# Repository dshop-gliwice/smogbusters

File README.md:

# smogbusters
Air monitoring project

Links:
 - particulate matter (PM) map: http://smogbusters.org/
 - charts: http://grafana.smogbusters.org/dashboard/db/measurements?refresh=10s&orgId=1
 - list of components: [bom.md](./docs/bom.md)

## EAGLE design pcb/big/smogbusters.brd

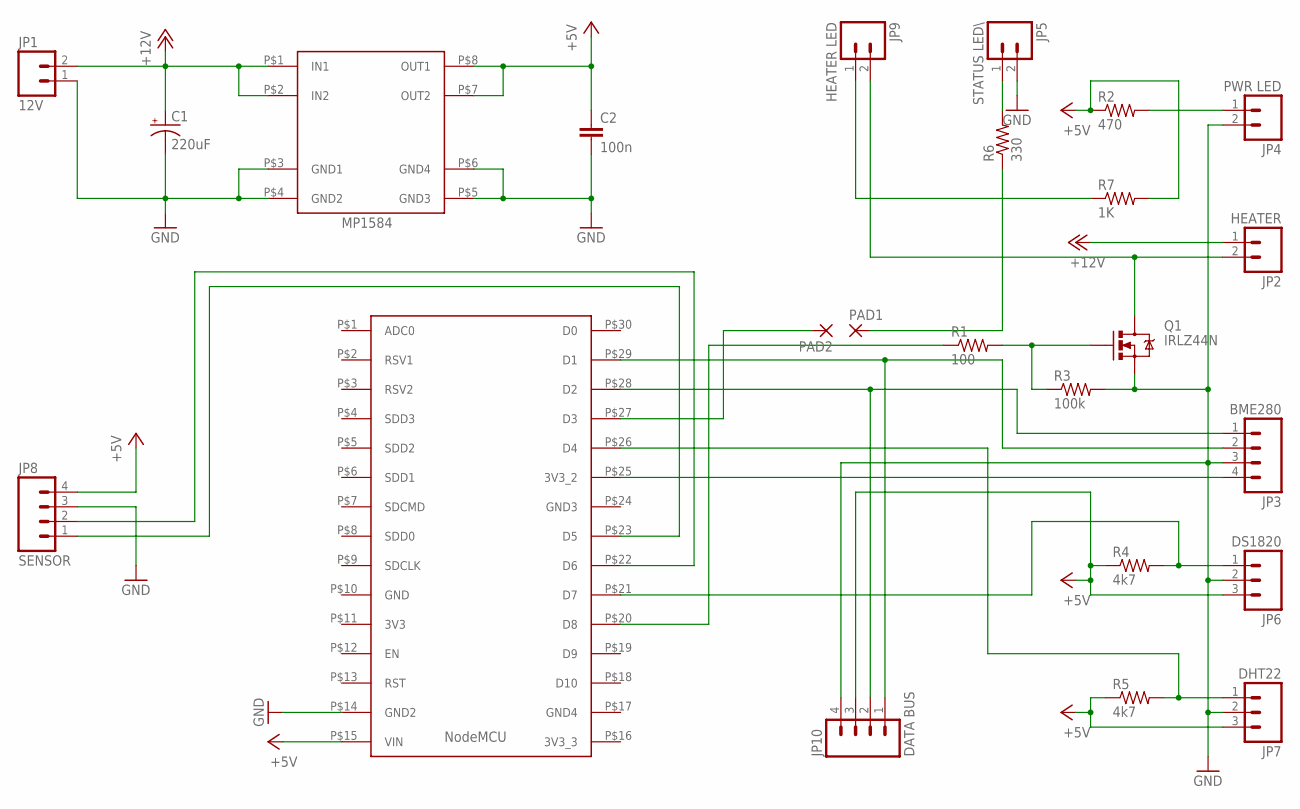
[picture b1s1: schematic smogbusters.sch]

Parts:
C1: 220uF; CPOL-RADIAL-100UF-25V
C2: 100n; C5B2.5
JP1: 12V; SCREWTERMINAL-5MM-2
JP2: HEATER; SCREWTERMINAL-5MM-2
JP3: BME280; 1X04
JP4: PWR LED; 1X02
JP5: STATUS LED\; 1X02
JP6: DS1820; 1X03
JP7: DHT22; 1X03
JP8: SENSOR; MOLEX-1X4
JP9: HEATER LED; 1X02
JP10: DATA BUS; 1X04
PAD1, PAD2: 1,6/0,8
Q1: IRLZ44N; TO220V
R1: 100; AXIAL-0.3
R2: 470; AXIAL-0.3
R3: 100k; AXIAL-0.3
R4, R5: 4k7; AXIAL-0.3
R6: 330; AXIAL-0.3
R7: 1K; AXIAL-0.3
U$1: NODEMCU
U$2: MP1584

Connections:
+5V: C2.1, JP6.3, JP7.3, JP8.4, JP10.3, R2.P$1 (1), R4.P$1 (1), R5.P$1 (1), R7.P$2 (2), U$1.P$15 (VIN), U$2.P$7 (OUT2), U$2.P$8 (OUT1)
+12V: C1.1 (+), JP1.2, JP2.1, U$2.P$1 (IN1), U$2.P$2 (IN2)
GND: C1.2 (-), C2.2, JP1.1, JP3.3, JP4.2, JP5.2, JP6.2, JP7.2, JP8.3, JP10.4, Q1.3 (S), R3.P$2 (2), U$1.P$14 (GND2), U$2.P$3 (GND1), U$2.P$4 (GND2), U$2.P$5 (GND3), U$2.P$6 (GND4)
unnamed: JP2.2, JP9.2, Q1.2 (D)
unnamed: JP6.1, R4.P$2 (2), U$1.P$21 (D7)
unnamed: Q1.1 (G), R1.P$2 (2), R3.P$1 (1)
unnamed: JP5.1, R6.P$2 (2)
unnamed: JP3.4, U$1.P$25 (3V3_2)
unnamed: JP8.1, U$1.P$23 (D5)
unnamed: JP8.2, U$1.P$22 (D6)
unnamed: R1.P$1 (1), U$1.P$20 (D8)
unnamed: JP7.1, R5.P$2 (2), U$1.P$26 (D4)
unnamed: PAD1.1, R6.P$1 (1)
unnamed: JP9.1, R7.P$1 (1)
unnamed: PAD2.1, U$1.P$27 (D3)
unnamed: JP4.1, R2.P$2 (2)
unnamed: JP3.1, JP10.2, U$1.P$28 (D2)
unnamed: JP3.2, JP10.1, U$1.P$29 (D1)

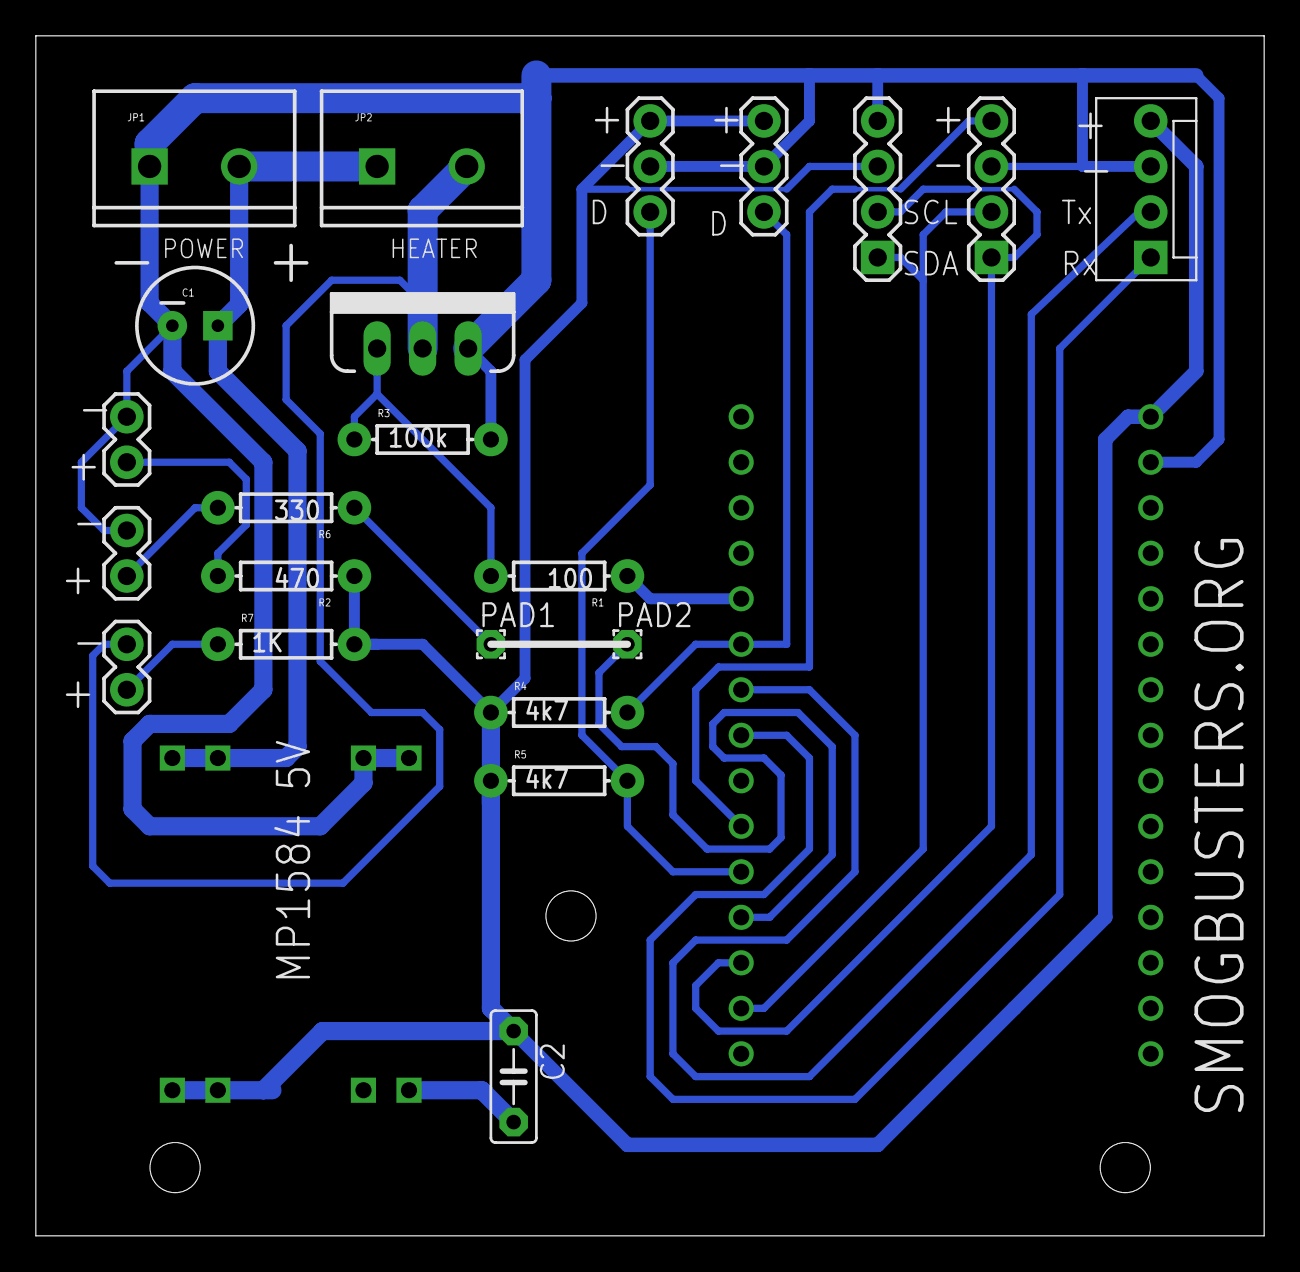
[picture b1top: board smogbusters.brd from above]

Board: 1 copper layer, 68.6 x 67.0 mm, 24 parts (1 on the bottom side), 18 nets.

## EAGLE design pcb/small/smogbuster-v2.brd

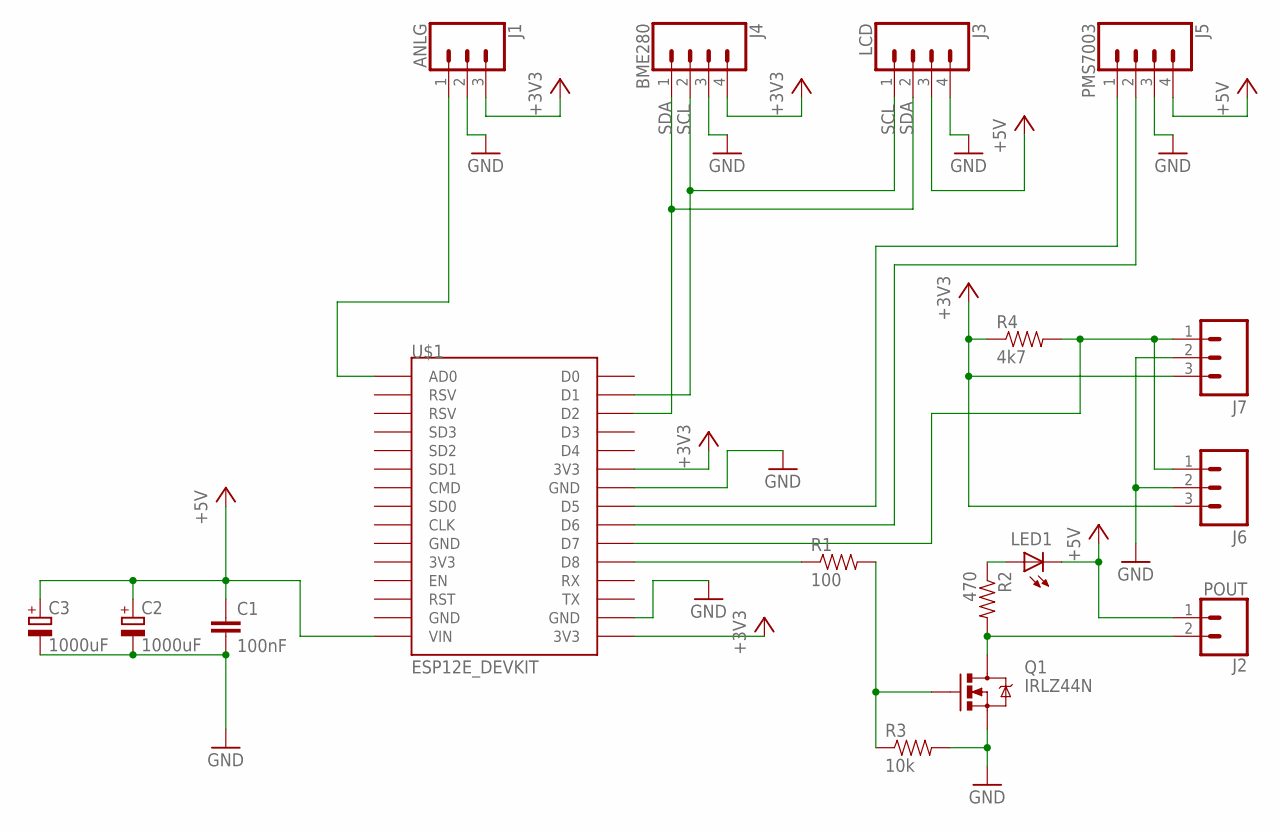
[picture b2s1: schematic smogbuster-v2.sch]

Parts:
C1: 100nF; CAP-PTH-5MM
C2, C3: 1000uF; E2,5-7
J1: ANLG; 1X03
J2: POUT; 1X02
J3: LCD; 1X04
J4: BME280; 1X04
J5: PMS7003; 1X04
J6, J7: M03PTH; 1X03
LED1: LED3MM
Q1: IRLZ44N; TO220V
R1: 100; AXIAL-0.3
R2: 470; AXIAL-0.3
R3: 10k; AXIAL-0.3
R4: 4k7; AXIAL-0.3
U$1: ESP12E_DEVKIT

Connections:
+3V3: J1.3, J4.4, J6.3, J7.3, R4.P$1 (1), U$1.3V3@1 (3V3), U$1.3V3@2 (3V3)
+5V: C1.1, C2.+, C3.+, J2.1, J3.3, J5.4, LED1.K (C), U$1.VIN
DQ: J6.1, J7.1, R4.P$2 (2), U$1.D7
GND: C1.2, C2.-, C3.-, J1.2, J3.4, J4.3, J5.3, J6.2, J7.2, Q1.3 (S), R3.P$2 (2), U$1.GND@2 (GND), U$1.GND@3 (GND)
unnamed: J2.2, Q1.2 (D), R2.P$2 (2)
unnamed: Q1.1 (G), R1.P$2 (2), R3.P$1 (1)
unnamed: J1.1, U$1.AD0
unnamed: R1.P$1 (1), U$1.D8
unnamed: LED1.A, R2.P$1 (1)
RX: J5.1, U$1.D5
SCL: J3.1, J4.2, U$1.D1
SDA: J3.2, J4.1, U$1.D2
TX: J5.2, U$1.D6

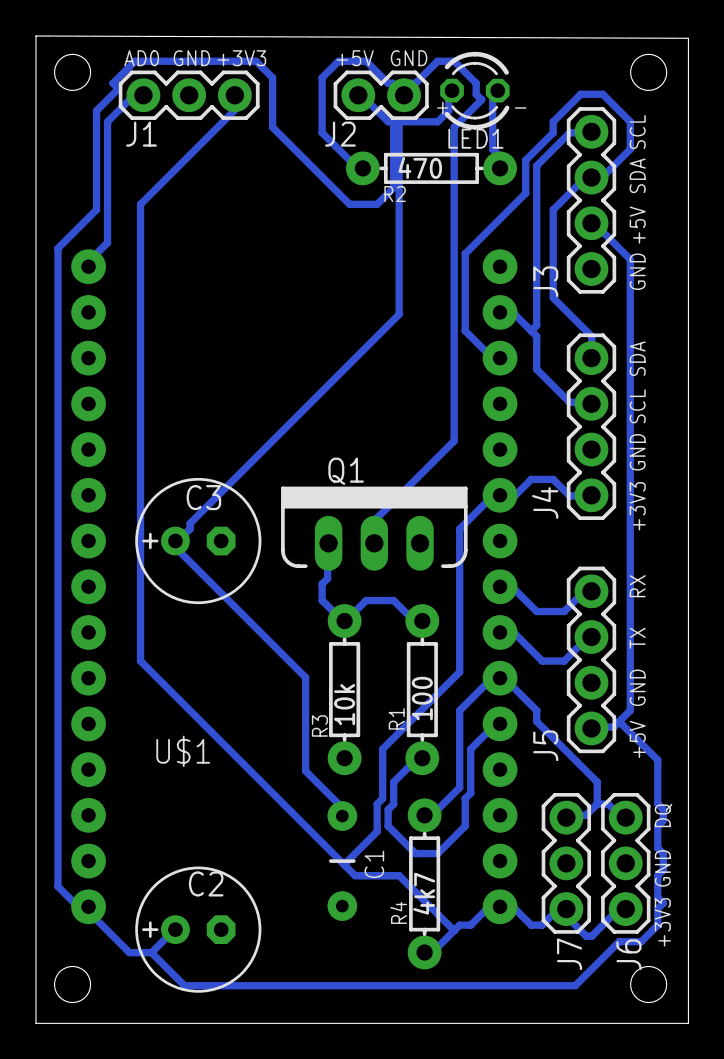
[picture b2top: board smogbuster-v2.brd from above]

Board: 1 copper layer, 36.2 x 54.9 mm, 17 parts (0 on the bottom side), 13 nets.

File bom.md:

# smogbusters
Air monitoring project

* NodeMCU
  * https://www.aliexpress.com/item/1PCS-New-Wireless-Module-Nod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
  * https://botland.com.pl/moduly-wifi/4450-modul-wifi-esp8266-n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


* Mosfet IRLZ44N
  * https://www.aliexpress.com/item/10PCS-IRLZ44N-IRLZ44-TO-220-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
  * https://botland.com.pl/n-mosfet/1950-n-mosfet-irlz44n-tht.ht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


* DC Power Supply Socket Female - 5.5 x 2.1mm
  * https://www.aliexpress.com/item/10Pcs-5-5-x-2-1mm-DC-Power-S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
  * https://botland.com.pl/przewody-i-zlacza-zasilajace/9352-gni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


* 15 Pin Female Single Row Straight Header Strip 2.54mm Pitch  
  * https://www.aliexpress.com/snapshot/0.html?spm=a2g0s.9042311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


* ARK connector
  * https://www.aliexpress.com/item/20pcs-KF301-2-Pin-Screw-Term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
  * https://botland.com.pl/zlacza-ark/810-zlacze-kf301-raster-5-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


* Wires
  * https://botland.com.pl/przewody-polaczeniowe/2713-przewod-ze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


* Power supply
  * https://www.aliexpress.com/item/S103-1pc-New-AC-100-240V-to-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


* BME280
  * https://www.aliexpress.com/item/BME280-Digital-Sensor-Temper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
  * https://botland.com.pl/czujniki-temperatury/165-czujnik-temp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


* DS18B20
  * https://www.aliexpress.com/item/new-and-original-DS18B20-18B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


* PLANTOWER Laser DUST SENSOR PMS7003  
  * https://www.aliexpress.com/item/PLANTOWER-Laser-PM2-5-DUST-S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

* IDC adapter
  * https://kamami.pl/zlacza-inne/564553-adapter-idc10-127mm-na-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

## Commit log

2017-02-24 DHT read and send to server
2017-02-27 EEPROM config
2017-03-02 PMS5003 working
2017-03-23 Libraries
2017-03-23 Client for sending measurement to api gateway via http
2017-03-23 Sending measurements - further changes
2017-03-23 Add BME280 sensor support
2017-03-25 send PMS data
2017-04-05 add debug data, fix url
2017-04-06 add automatic uuid generation
2017-04-06 add pm1 measurement
2017-04-13 DS1820 support - pin D7
2017-04-23 Heater definition
2018-02-22 First version of BOM
2018-02-22 Fix formatting
2018-02-22 fix formatting #2
2018-02-22 Update links
2018-03-08 Add pcb
2018-07-03 improve 3d printed parts
2018-07-23 Add case for bme280
2018-07-23 Fix case for bme280
2018-07-24 bme280 case update
2018-07-25 Add support for status led
2018-09-26 Adapter for bme280 by dfrobot
2018-09-26 Bulk upgrade
    This should be divided into multiple commits. Sorry…
    - lcd support
    - settings for wifi and bme280 are now stored in eeprom
    - extended serial commands
    - cleanup
2018-09-27 Add NewLiquidCrystal library
2018-10-01 Use DNS name instead of IP for gateway URL
2018-10-01 Heater - working copy. TODO - safe fallback when no sensor is present or sensor is broken
2018-10-01 Add OTA update
2018-10-03 Working heater, PMS library used
2018-10-03 Add heaterVoltage to eeprom
2018-10-03 Add PMS library
2018-10-03 Move Firmware version to "data" section
2018-10-10 add missing libraries
2018-10-10 Add new adapters for BME280
2018-10-11 Improve handling of disconnected sensors
2018-10-11 Fix adapter for bme280-narrow
2018-10-12 Add config flag to control lcd
2018-11-18 Add case for pms7003
2018-11-19 Add drill template
2018-12-02 Improve case for pms7003
2018-12-02 Improve resolution for ds18b20
2019-01-04 Fix var names
2019-01-07 Change api url
2019-01-07 Add smaller version of PCB
2019-01-14 PCB fixes acc. to ticket #1
2019-11-06 Production PCB
2019-12-12 Improve bme280-dfrobot adapter
2019-12-12 Update documentation
2019-12-12 Add links to README.md
2019-12-12 Add pdf preview for big pcb
2019-12-12 Add device assembly documentation
2019-12-12 Change main photo

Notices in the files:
parts and their libraries:
SparkFun-Capacitors: Licensing: Creative Commons ShareAlike 4.0 International - https://creativecommons.org/licenses/by-sa/4.0
